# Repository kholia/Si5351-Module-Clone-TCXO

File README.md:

#### Notes

Note: We are using KiCad 7.0.x version to build this project.

[UPDATE] The design was validated on 27th-Feb-2023. It works really well for
WSPR @ 28 MHz where the original Adafruit Si5351 module is barely usable.

#### JLC PCBA files

- [Gerbers](./Adafruit-Si5351A-v3/jlcpcb/production_files/GERBER-Adafruit-Si5351A.zip)
- [BOM](./Adafruit-Si5351A-v3/jlcpcb/production_files/BOM-Adafruit-Si5351A.csv)
- [CPL](./Adafruit-Si5351A-v3/jlcpcb/production_files/CPL-Adafruit-Si5351A.csv)

#### PCB render

#### BOM Sources

- https://www.lcsc.com/ - MS5351M

- https://www.comkey.in/ - SMD passives

- https://www.ktron.in/ - SMA connectors for cheap

- https://www.semikart.com/ - TCXOs

Note: International buyers can buy from DigiKey or Mouser.

#### Credits

- Sambhu Dharmadevan (VU3KQF)

- Dhiru Kholia (VU3CER)

#### Supported TCXO Modules

- [DEFAULT] KDS Daishinku 1XTW26000MAA (26 MHz)

- YXC Crystal Oscillators OW2EL89CENUXK7YLC-25M

- huaxindianzi 3T025000VX - 25 MHz

- Jauch Quartz O 25,0-JT32C-A-K-3,3-LF

- Abracon ASTX-H11-25.000MHZ-T

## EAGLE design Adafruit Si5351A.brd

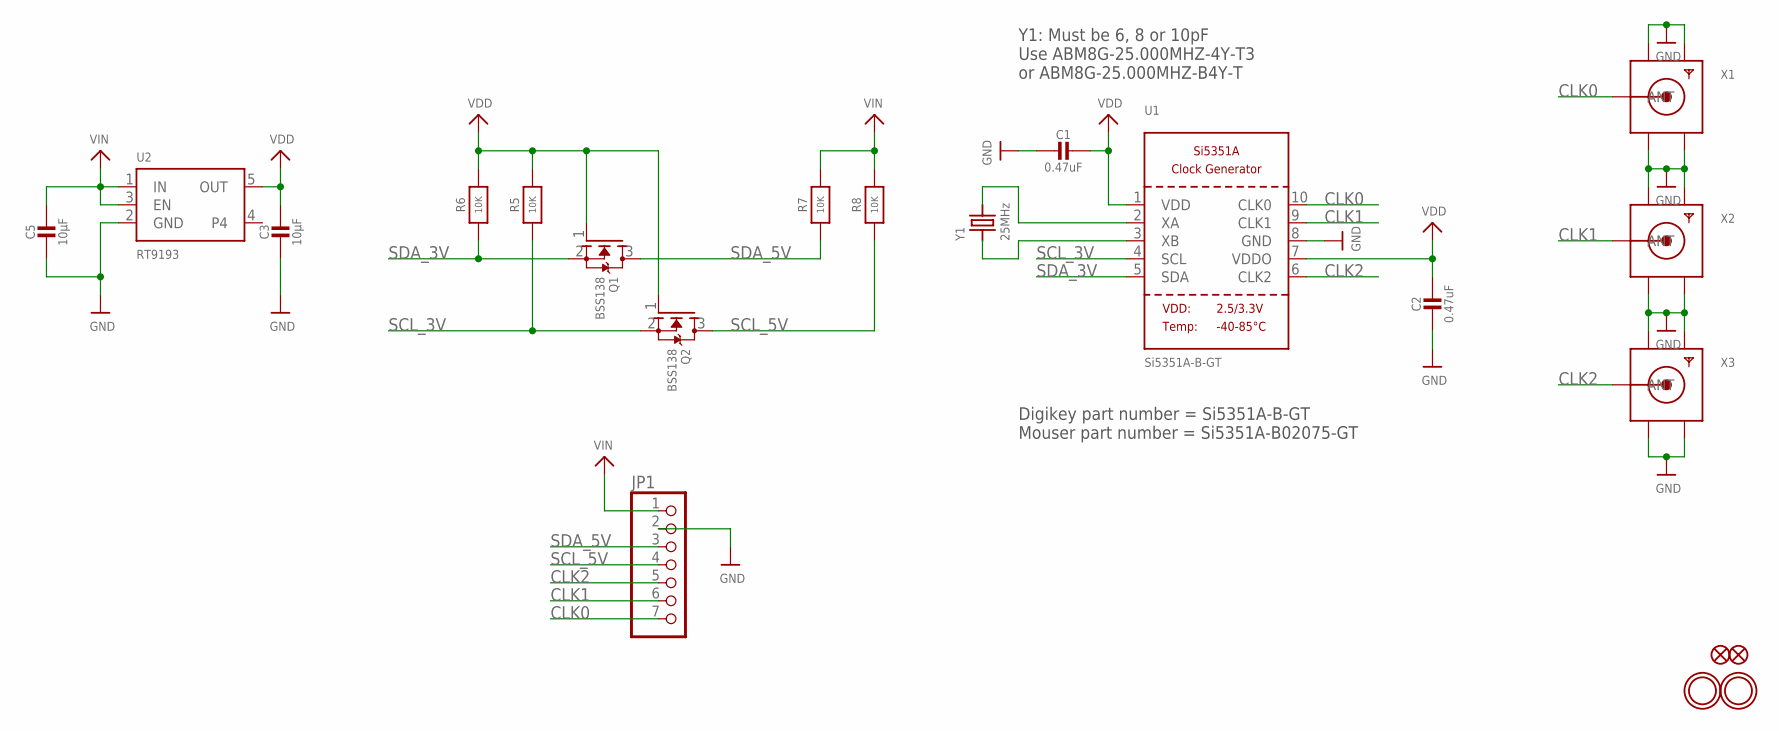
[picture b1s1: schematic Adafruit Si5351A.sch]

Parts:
C1, C2: 0.47uF; 0805-NO
C3, C5: 10µF; 0805-NO
FID1, FID2: FIDUCIAL""; FIDUCIAL_1MM
JP1: HEADER-1X7THICKER; 1X07_ROUND_76
Q1, Q2: BSS138; SOT23-WIDE
R5, R6, R7, R8: 10K; 0805-NO
U1: Si5351A-B-GT; MSOP10
U2: RT9193; SOT23-5
U$10, U$11: MOUNTINGHOLE2.5; MOUNTINGHOLE_2.5_PLATED
X1, X2, X3: SMACONNECTOR_EDGE; SMA_EDGELAUNCH
Y1: 25MHz; CRYSTAL_3.2X2.5

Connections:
CLK0: JP1.7, U1.10 (CLK0), X1.P (ANT)
CLK1: JP1.6, U1.9 (CLK1), X2.P (ANT)
CLK2: JP1.5, U1.6 (CLK2), X3.P (ANT)
GND: C1.2, C2.2, C3.2, C5.2, JP1.2, U1.8 (GND), U2.2 (GND), X1.GND@1 (GND4), X1.GND@2 (GND3), X1.GND@3 (GND2), X1.GND@4 (GND1), X2.GND@1 (GND4), X2.GND@2 (GND3), X2.GND@3 (GND2), X2.GND@4 (GND1), X3.GND@1 (GND4), X3.GND@2 (GND3), X3.GND@3 (GND2), X3.GND@4 (GND1)
unnamed: U1.3 (XB), Y1.1
unnamed: U1.2 (XA), Y1.2
SCL_3V: Q2.2 (S), R5.1, U1.4 (SCL)
SCL_5V: JP1.4, Q2.3 (D), R8.1
SDA_3V: Q1.2 (S), R6.1, U1.5 (SDA)
SDA_5V: JP1.3, Q1.3 (D), R7.1
VDD: C1.1, C2.1, C3.1, Q1.1 (G), Q2.1 (G), R5.2, R6.2, U1.1 (VDD), U1.7 (VDDO), U2.5 (OUT)
VIN: C5.1, JP1.1, R7.2, R8.2, U2.1 (IN), U2.3 (EN)

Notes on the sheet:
Digikey part number = Si5351A-B-GT Mouser part number = Si5351A-B02075-GT
Y1: Must be 6, 8 or 10pF Use ABM8G-25.000MHZ-4Y-T3 or ABM8G-25.000MHZ-B4Y-T

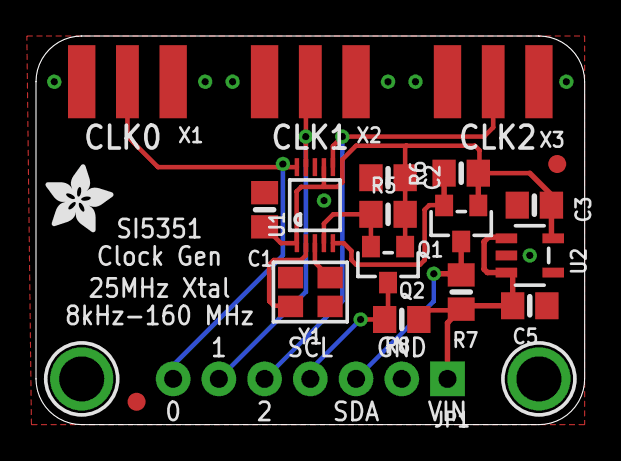
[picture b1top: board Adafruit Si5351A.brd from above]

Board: 2 copper layers, 30.5 x 21.6 mm, 23 parts (1 on the bottom side), 12 nets.

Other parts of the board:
U$12: ADAFRUIT_3.5MM
U$23: ADAFRUIT_TEXT_20MM

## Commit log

2016-08-04 init
2023-01-12 Native TCXO support
    Also add experimental support for 'KDS Daishinku 1XTW26000MAA' TCXO.
2023-12-05 KDS Daishinku 1XTW26000MAA TCXO is default now
2025-04-17 More compliant product
2025-07-23 Make 'Si5351-Trimmed-Module*' public
2026-02-21 Adafruit-Si5351A-v6

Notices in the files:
parts and their libraries:
microbuilder: This work is placed in the public domain, and may be freely used for commercial and non-commercial work with the following conditions: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
